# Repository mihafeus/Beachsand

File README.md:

# Beachsand
Project Beachsand is all about low-power easy to set-up RF sensor networks. At the moment it consists of SenseGrain and  SandCasle, with ActGrain coming some time in the future. 

The SenseGrain is an Attiny85 with an RF transmitter and a battery. The SandCastle is an Arduino with an RF receiver. Once assembled the only thing the user needs to do is select the update frequency. At the moment those are continuous, 5 sec, 30 sec, 5 min, 30 min, 2h, 6h, 24h and on interrupt. The update frequency has a great affect on the battery life - on continuous mode the battery should last a good month, on all the time modes 3-4 years and on interrupt up to 30 years (theoretically). After the initial setup all the user has to do is add the analog sensor or switch to the SenseGrain. The last step is to leave the SenseGrain in the location where it needs to measure things and then forget about it for a very long time.

The SenseGrain then keeps transmitting it’s name and the value from the analog sensor according to the intervals it was set up to. Those values are then received by the SandCastle and can from there be used for whatever application they are needed. One SandCastle can receive values from multiple SenseGrains.

TO DO:
- ActGrain remote wakeup and auto-pair
- Improve documentation
- Visualize the set-up process
- Create direct connections between SenseGrain and ActGrain
- Create SandCastle Arduino shield with Wi-fi and SD-card support, for logging and sending values without the need of a PC

Wishlist:
- Web dashboard
- Solar power
- Mesh network

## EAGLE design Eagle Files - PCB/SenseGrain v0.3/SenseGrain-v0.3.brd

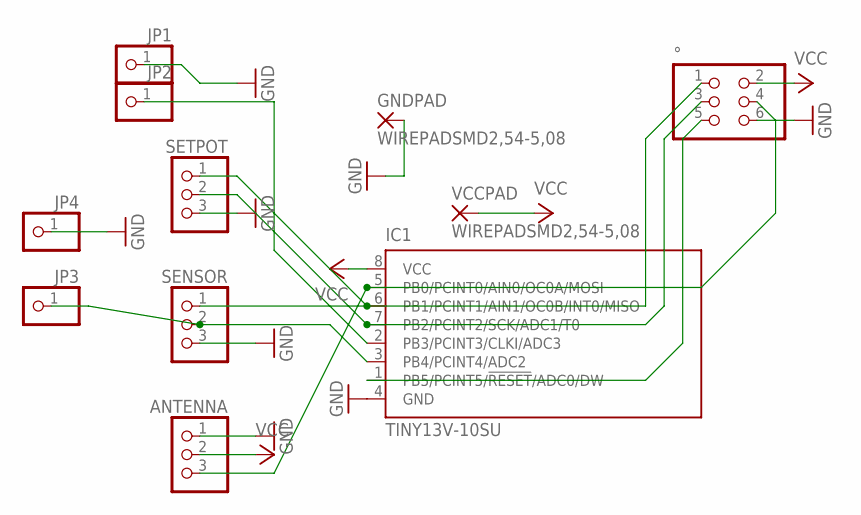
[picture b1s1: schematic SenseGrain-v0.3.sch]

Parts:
ANTENNA: PINHD-1X3CB; 1X03-CLEANBIG
GNDPAD: WIREPADSMD2,54-5,08; SMD2,54-5,08
IC1: TINY13V-10SU; 8S2
JP1, JP2, JP3, JP4: PINHD-1X1; 1X01
SENSOR: PINHD-1X3CB; 1X03-CLEANBIG
SETPOT: PINHD-1X3CB; 1X03-CLEANBIG
VCCPAD: WIREPADSMD2,54-5,08; SMD2,54-5,08
°: PINHD-2X3; 2X03

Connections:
GND: ANTENNA.1, GNDPAD.1, IC1.4 (GND), JP1.1, JP4.1, SENSOR.3, SETPOT.3, °.6
unnamed: IC1.6 (PB1/PCINT1/AIN1/OC0B/INT0/MISO), SENSOR.1, SETPOT.1, °.1
unnamed: ANTENNA.3, IC1.5 (PB0/PCINT0/AIN0/OC0A/MOSI), °.4
unnamed: IC1.3 (PB4/PCINT4/ADC2), JP3.1, SENSOR.2
unnamed: IC1.2 (PB3/PCINT3/CLKI/ADC3), JP2.1
unnamed: IC1.1 (PB5/PCINT5/!RESET!/ADC0/DW), °.5
unnamed: IC1.7 (PB2/PCINT2/SCK/ADC1/T0), SETPOT.2, °.3
VCC: ANTENNA.2, IC1.8 (VCC), VCCPAD.1, °.2

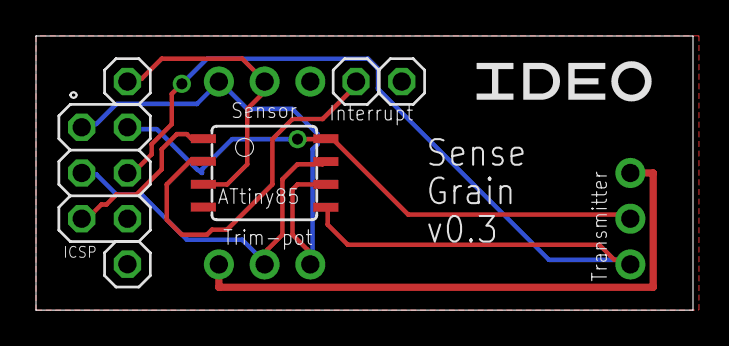
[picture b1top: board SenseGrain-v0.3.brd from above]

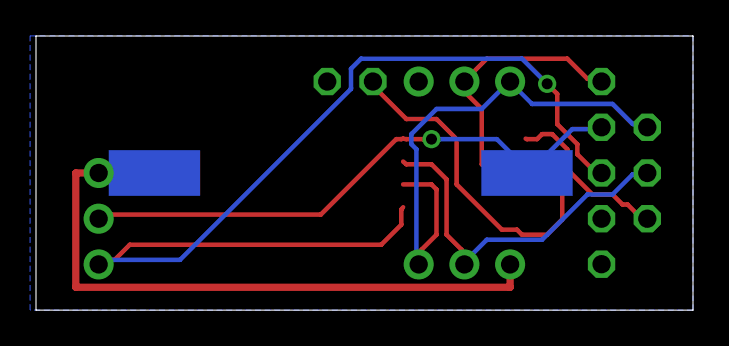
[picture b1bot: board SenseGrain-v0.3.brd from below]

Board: 2 copper layers, 36.5 x 15.2 mm, 11 parts (2 on the bottom side), 8 nets.

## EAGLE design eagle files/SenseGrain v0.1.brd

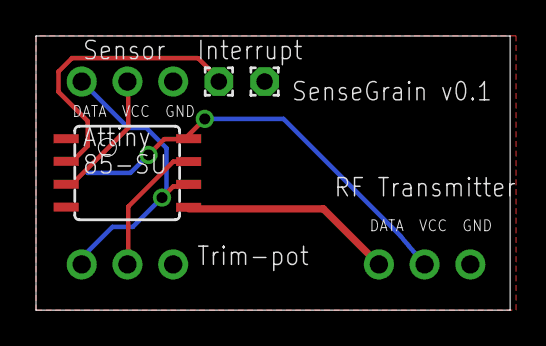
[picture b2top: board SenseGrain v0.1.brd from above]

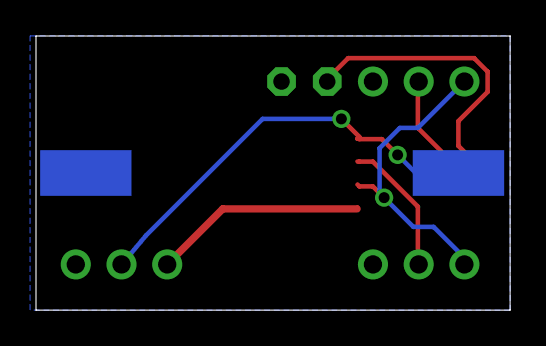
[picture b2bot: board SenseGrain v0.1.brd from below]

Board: 2 copper layers, 26.3 x 15.2 mm, 8 parts (2 on the bottom side), 7 nets.

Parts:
ANTENNA: 1X03-CLEANBIG
GNDPAD: WIREPADSMD2,54-5,08; SMD2,54-5,08
IC1: TINY13V-10SU; 8S2
PAD3, PAD4: 1,6/0,9
SENSOR: 1X03-CLEANBIG
SETPOT: 1X03-CLEANBIG
VCCPAD: WIREPADSMD2,54-5,08; SMD2,54-5,08

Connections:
GND: ANTENNA.1, GNDPAD.1, IC1.4, PAD4.1, SENSOR.3, SETPOT.3
unnamed: IC1.6, SENSOR.1, SETPOT.1
unnamed: ANTENNA.3, IC1.5
unnamed: IC1.3, SENSOR.2
unnamed: IC1.7, SETPOT.2
unnamed: IC1.2, PAD3.1
VCC: ANTENNA.2, IC1.8, VCCPAD.1

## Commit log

2015-03-27 Changed the name of the SenseGrain
2015-03-27 put files into own folder
2015-03-27 Updated project description
2015-03-27 Added libraries
2015-03-27 Added comments
2015-07-10 SenseGrain PCB v0.2
    Added Eagle files for SenseGrain v0.2 PCB together with Gerber files
2015-07-15 Added Fritzing files
    - Added Fritzing files
    - Updated TO-DO
    - renamed folders
2015-07-15 Improved communication protocol
    The name of the SenseGrain and the values are now being sent together
    and then split back up by the SandCastle
2015-07-15 Updated to-do
    Updated to-do and added wish list
2015-07-16 Improved SandCastle code
    Now you can plug in the receiver directly to the Arduino. Just don’t
    forget to cut the CS pin on the receiver
2015-07-20 New version of the PCB
2015-07-20 Updated SandCastle code
    Now you can plug the receiver straight into the Arduino
2015-08-17 Added missing Virtual Wire library and ATtiny hardware folder
    ATtiny folder was taken from here
    https://code.google.com/p/arduino-tiny/downloads/list
2015-08-20 SenseGrain: new features, auto-naming, code clean-up
    New threshold feature, auto name generation, code has been cleaned up
2015-08-20 Updated TO DO
    Taken a few thing off the TO DO list that I have already done
2015-08-20 Updated name generator
    Upload the name generator before you upload the SenseGrain code. That
    is, if you are tired of coming up with names.
